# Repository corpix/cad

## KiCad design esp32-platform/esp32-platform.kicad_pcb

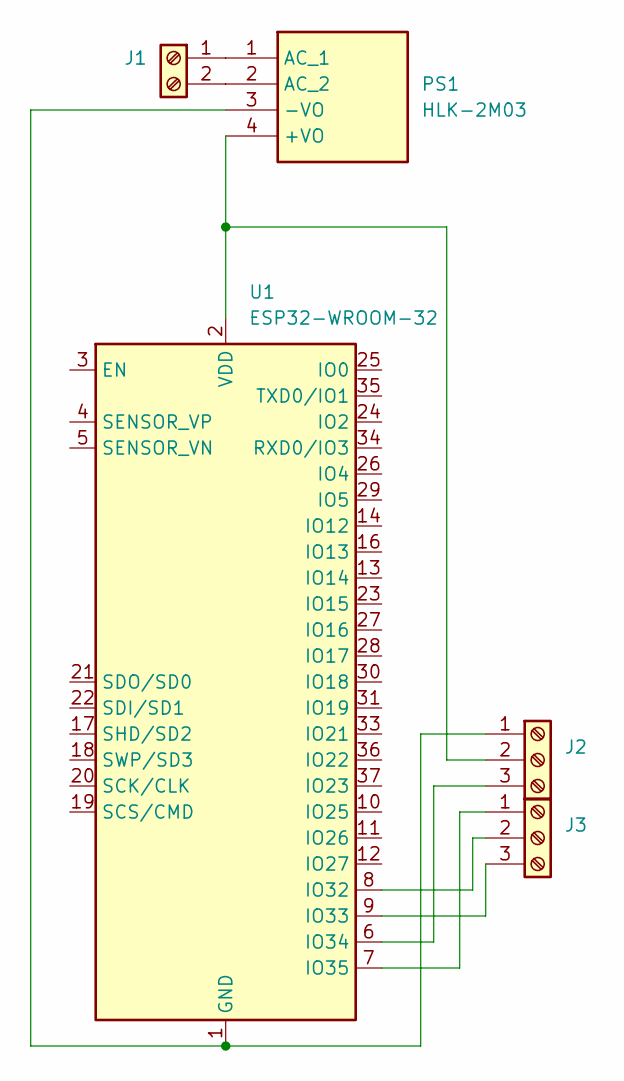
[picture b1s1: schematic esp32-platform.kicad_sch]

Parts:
J1: Screw_Terminal_01x02; Altech_AK300_1x02_P5.00mm_45-Degree
J2, J3: Screw_Terminal_01x03; Altech_AK300_1x03_P5.00mm_45-Degree
PS1: HLK-2M03; HLK2M03; Manufacturer_Part_Number HLK-2M03
U1: ESP32-WROOM-32

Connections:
unnamed: J1.1, PS1.1 (AC_1)
unnamed: J1.2, PS1.2 (AC_2)
unnamed: J2.1, PS1.3 (-VO), U1.1 (GND), U1.15 (GND), U1.38 (GND), U1.39 (GND)
unnamed: J2.2, PS1.4 (+VO), U1.2 (VDD)
unnamed: J2.3, U1.6 (IO34)
unnamed: J3.1, U1.7 (IO35)
unnamed: J3.2, U1.8 (IO32)
unnamed: J3.3, U1.9 (IO33)

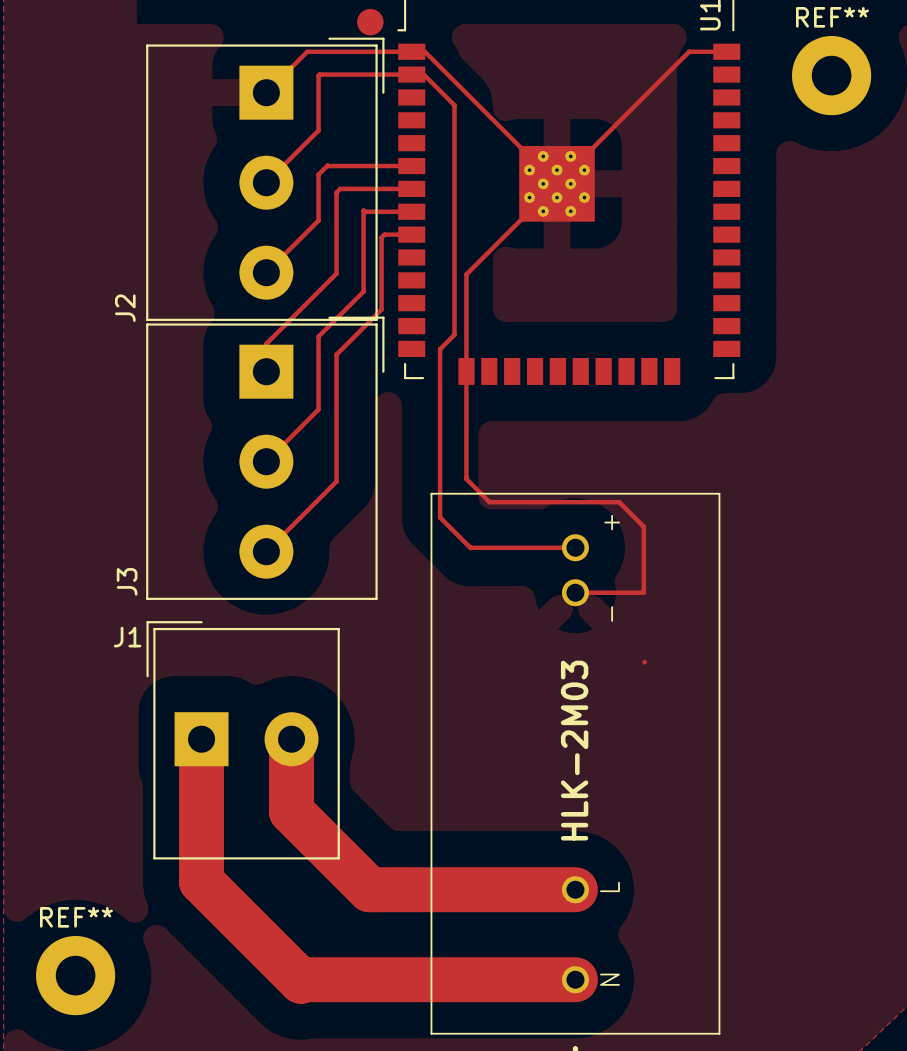
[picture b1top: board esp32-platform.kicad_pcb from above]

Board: 2 copper layers, 5 parts (0 on the bottom side), 8 nets.

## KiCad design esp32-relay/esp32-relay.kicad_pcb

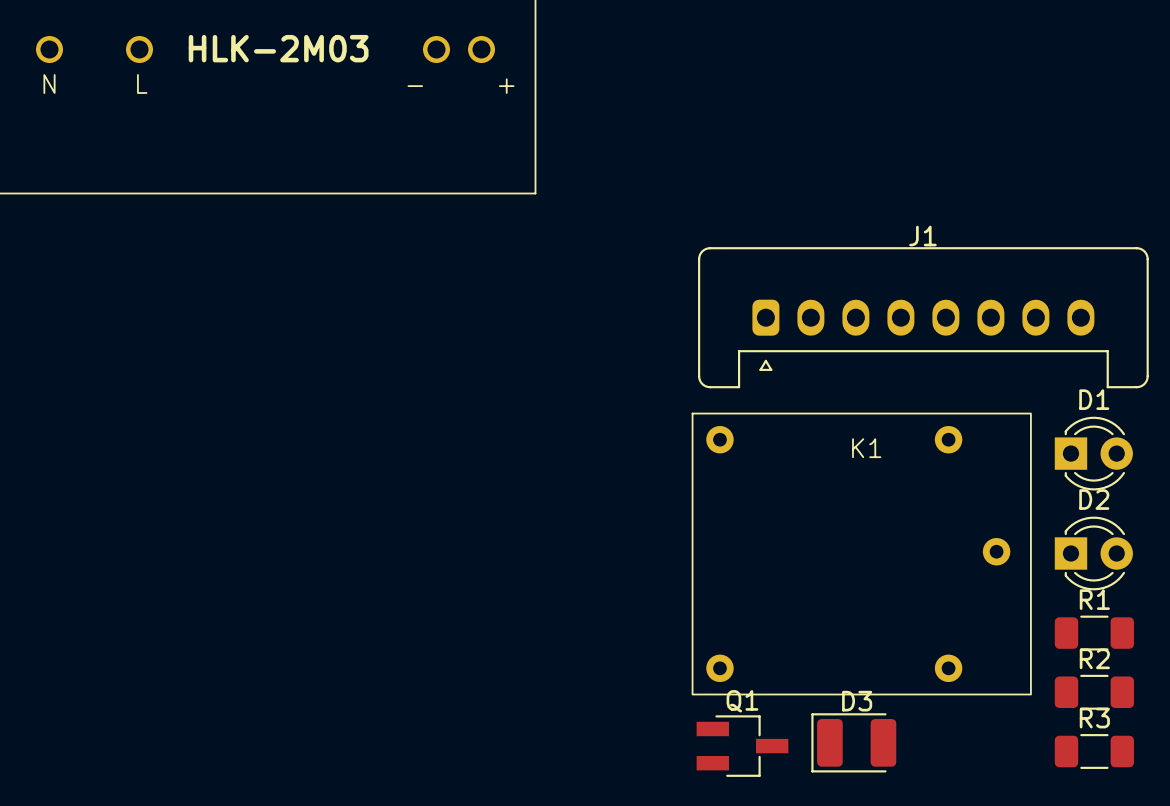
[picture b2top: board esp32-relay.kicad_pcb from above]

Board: 2 copper layers, 10 parts (0 on the bottom side), 7 nets, no tracks yet.

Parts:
D1, D2: LED; LED_D3.0mm
D3: D; D_1210_3225Metric_Pad1.42x2.65mm_HandSolder
J1: Conn_01x08_Pin, ESP32; Stocko_MKS_1658-6-0-808_1x8_P2.50mm_Vertical
K1: FL-3FF-S-Z
PS1: HLK-2M03; HLK2M03
Q1: PNP; SC-59_Handsoldering
R1, R2, R3: 1K; R_1206_3216Metric_Pad1.30x1.75mm_HandSolder

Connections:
+3.3V: J1.8, PS1.4 (+VO), R1.1
GND: D1.1 (K), D2.1 (K), D3.2 (A), J1.7, PS1.3 (-VO)
unnamed: D1.2 (A), R3.2
unnamed: D2.2 (A), R2.2
unnamed: D3.1 (K), Q1.1 (C), R3.1
unnamed: Q1.2 (B), R1.2
VCC: J1.6, Q1.3 (E), R2.1

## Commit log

2022-06-04 init
2022-07-27 improved mini-itx server case
2022-07-27 add concrete sink model
2022-07-27 add whiteboard marker handler
2022-07-27 add gitignore
2022-07-27 add stl files
2022-08-29 new mini itx frame
2022-08-29 wip sink frame
2022-09-20 whole bunch of new models :)
2023-04-07 save state
2023-05-15 konakovskiy updates
2023-06-11 planning konakovskiy office
2023-12-19 new cads
2024-09-30 lab assembly
